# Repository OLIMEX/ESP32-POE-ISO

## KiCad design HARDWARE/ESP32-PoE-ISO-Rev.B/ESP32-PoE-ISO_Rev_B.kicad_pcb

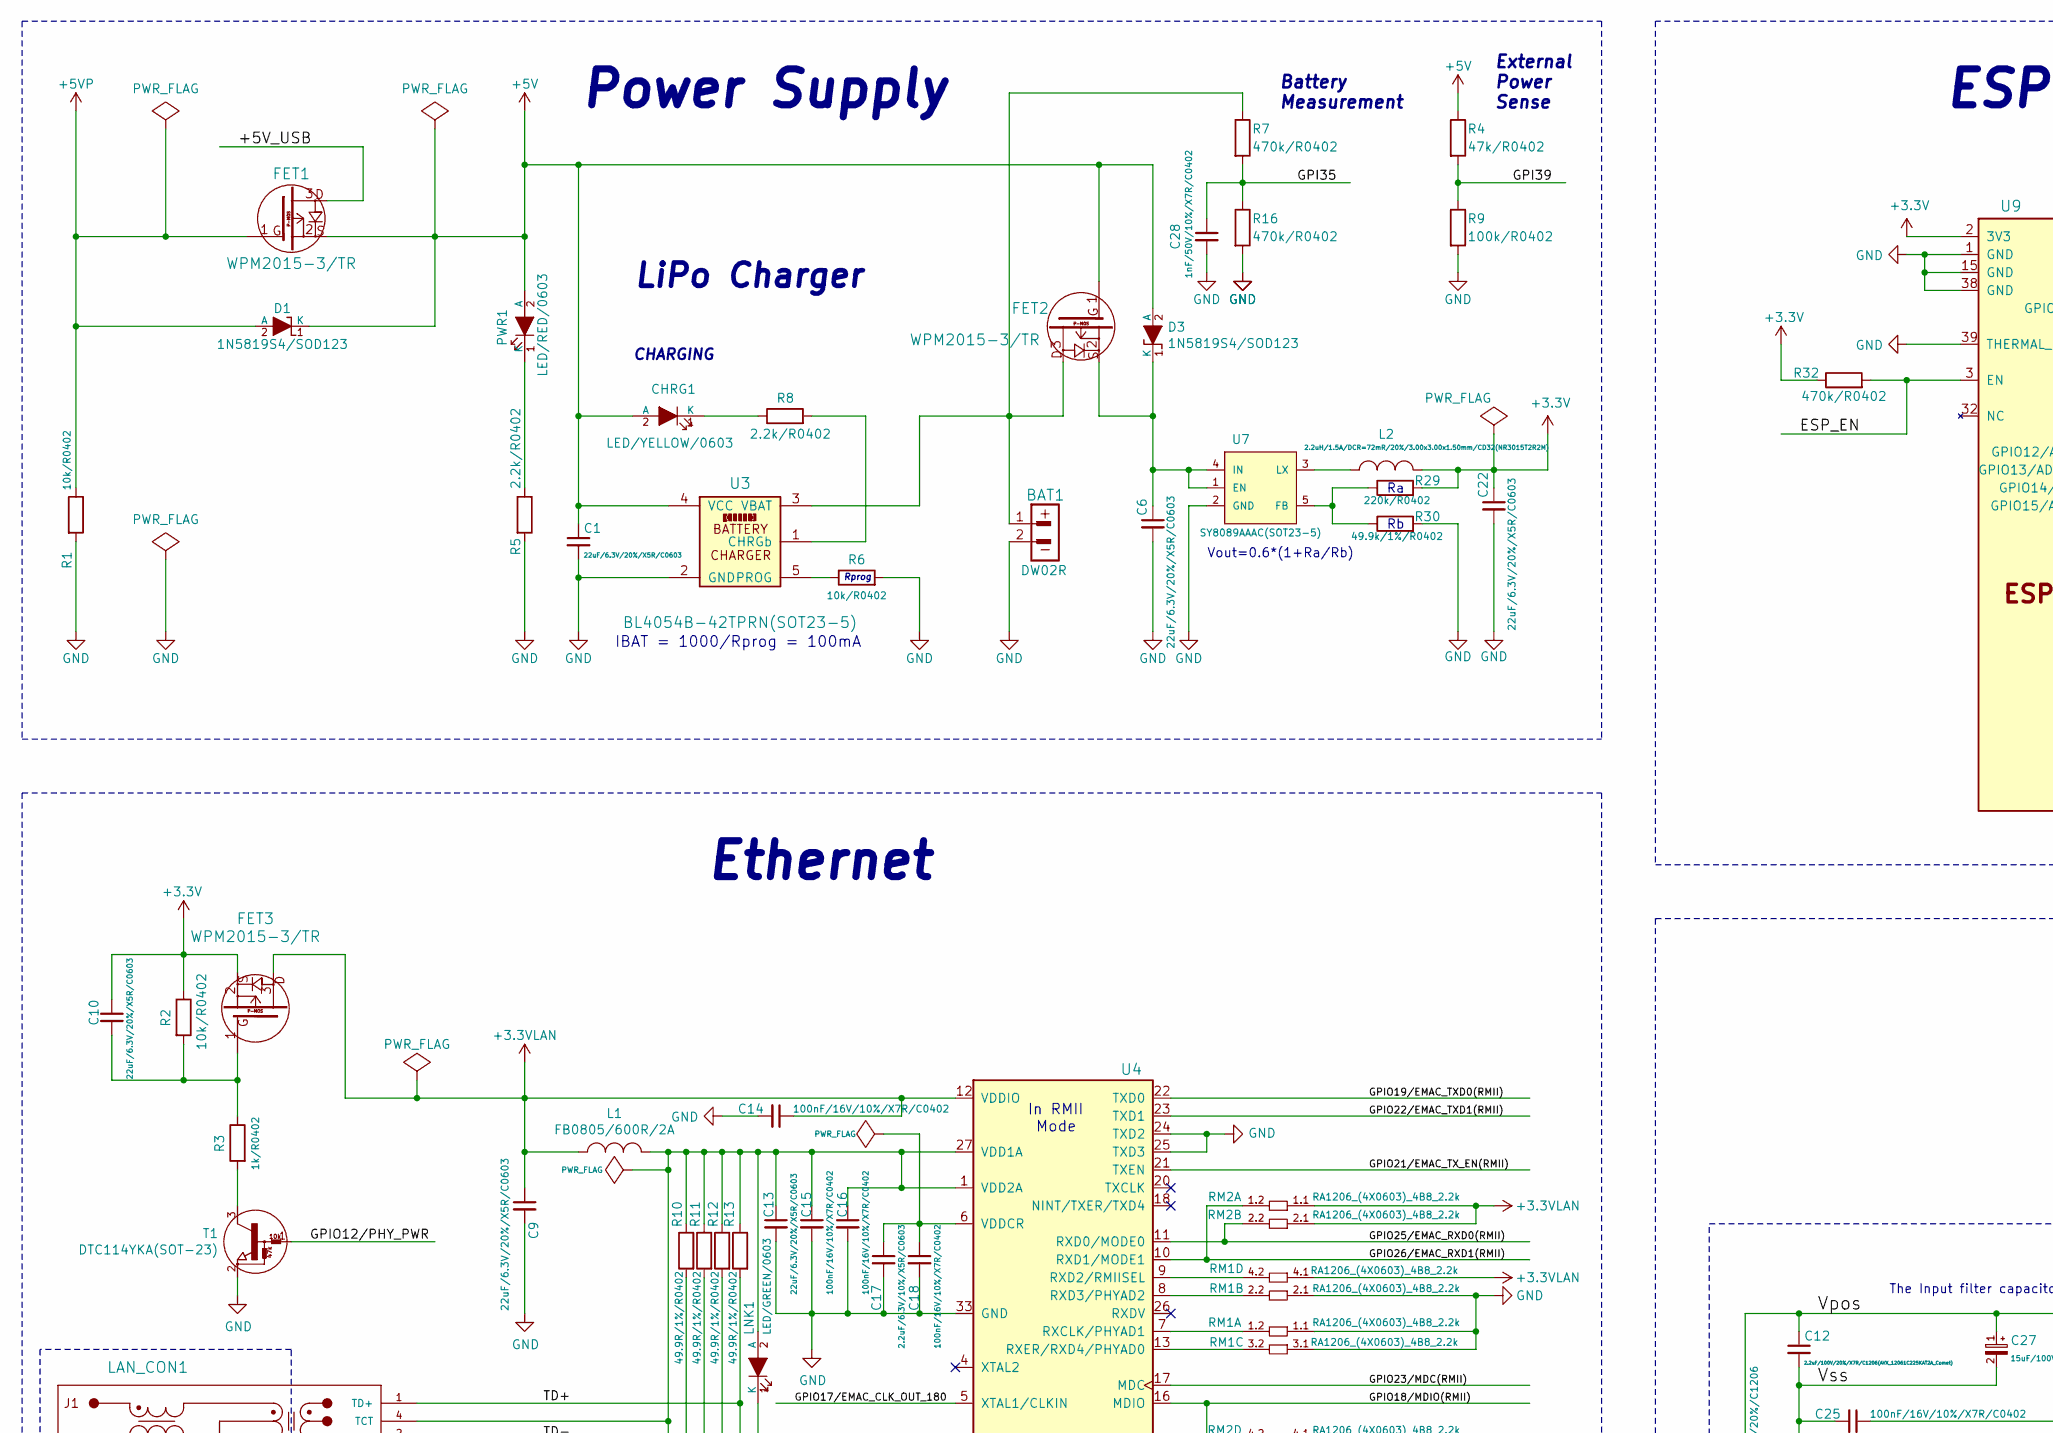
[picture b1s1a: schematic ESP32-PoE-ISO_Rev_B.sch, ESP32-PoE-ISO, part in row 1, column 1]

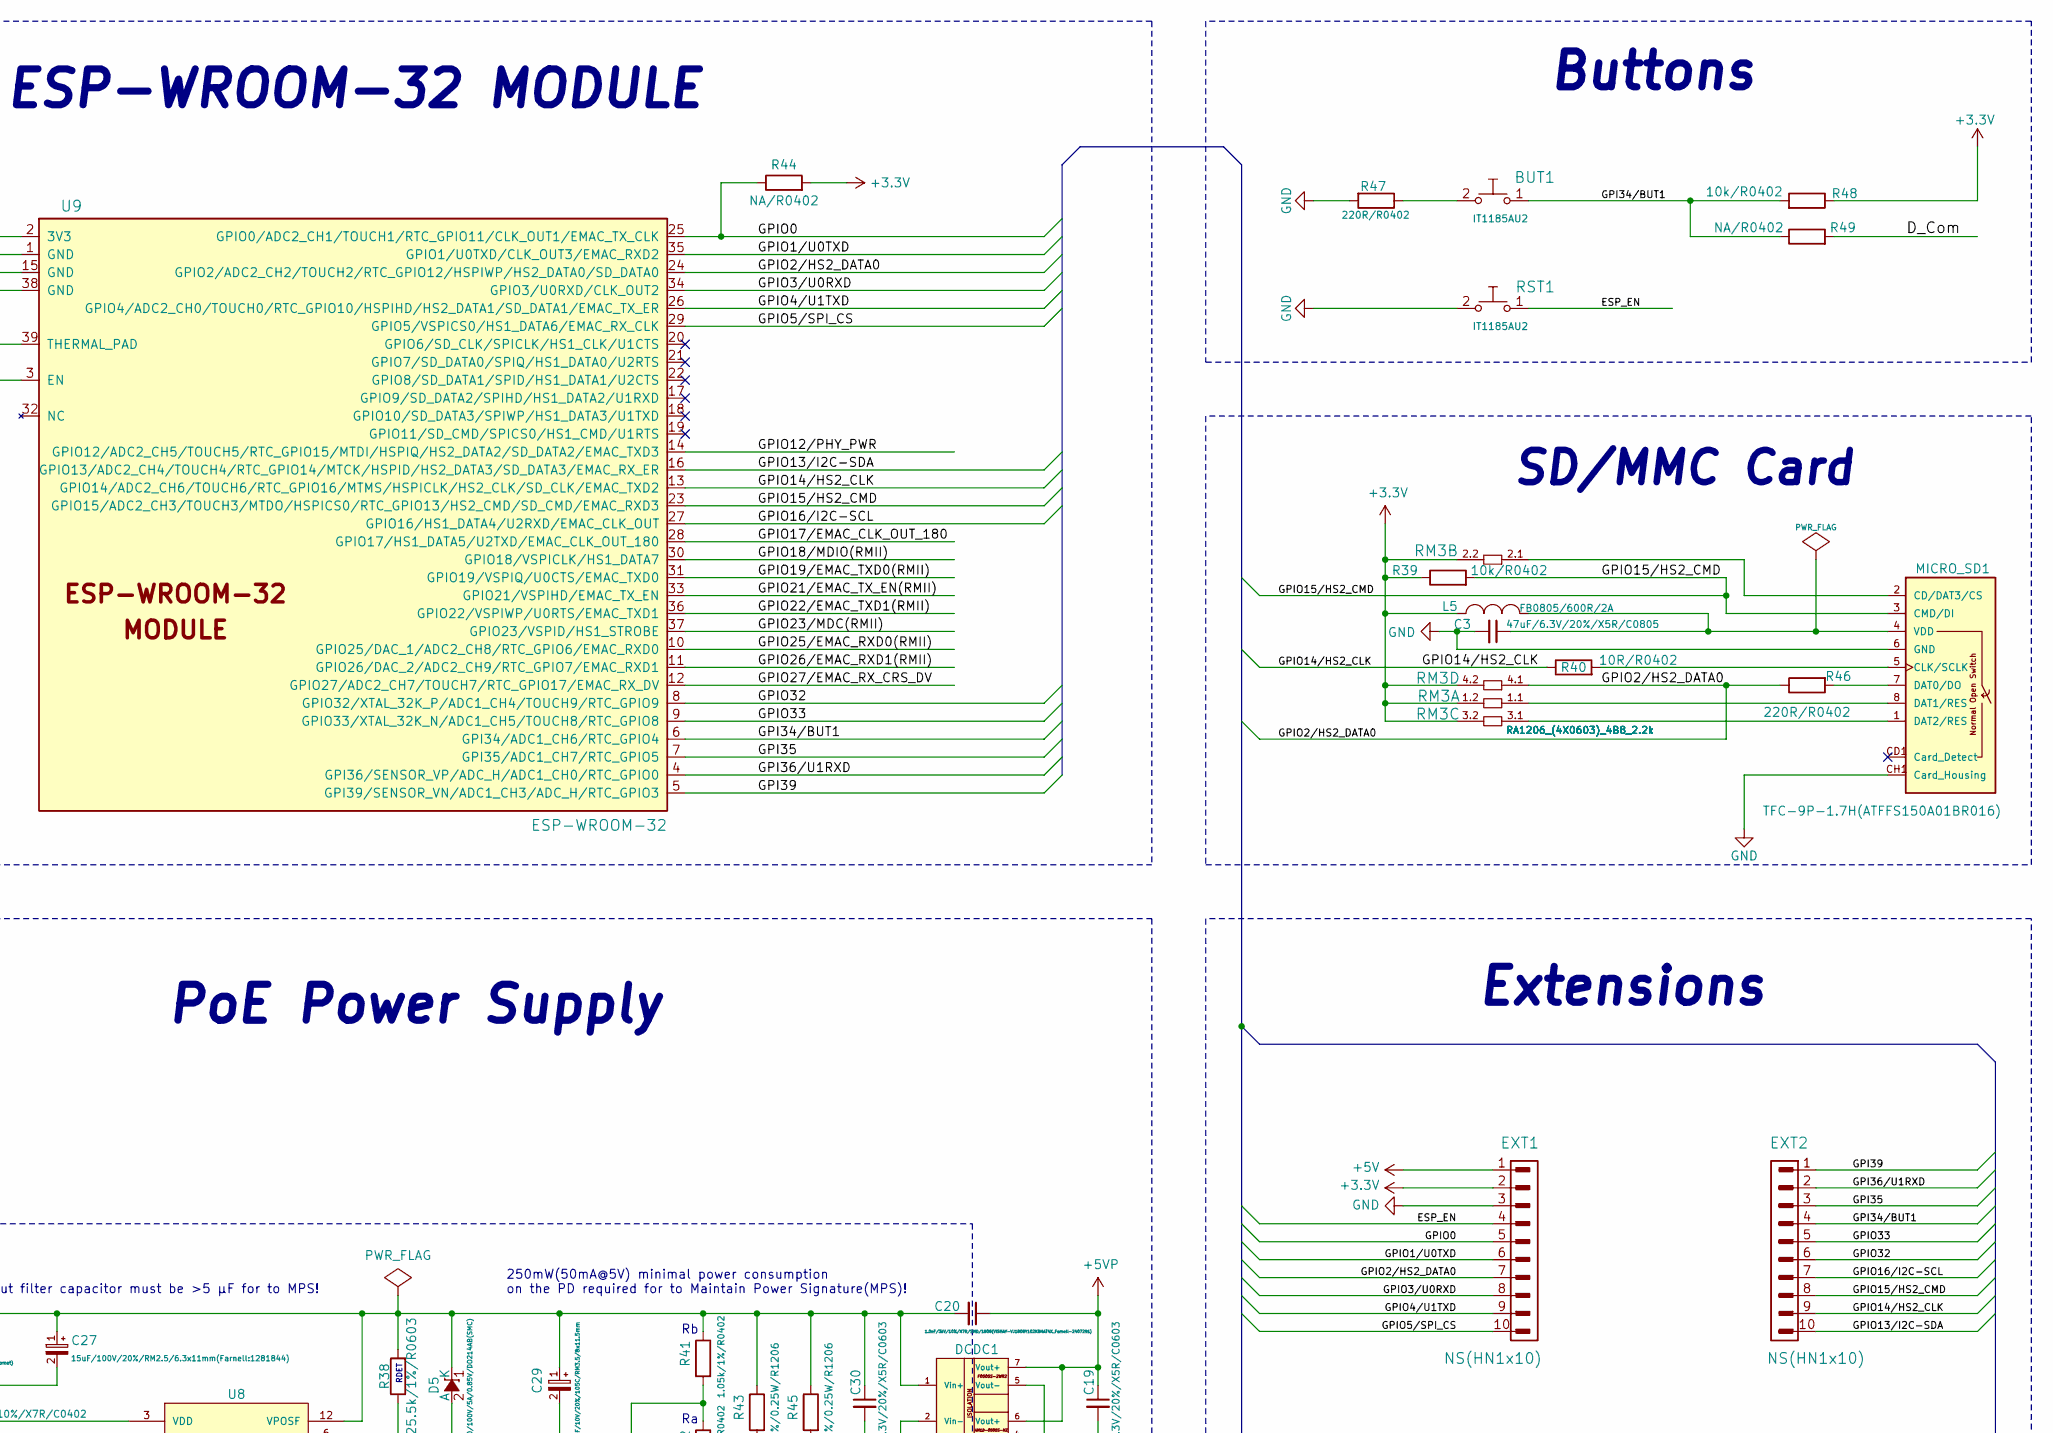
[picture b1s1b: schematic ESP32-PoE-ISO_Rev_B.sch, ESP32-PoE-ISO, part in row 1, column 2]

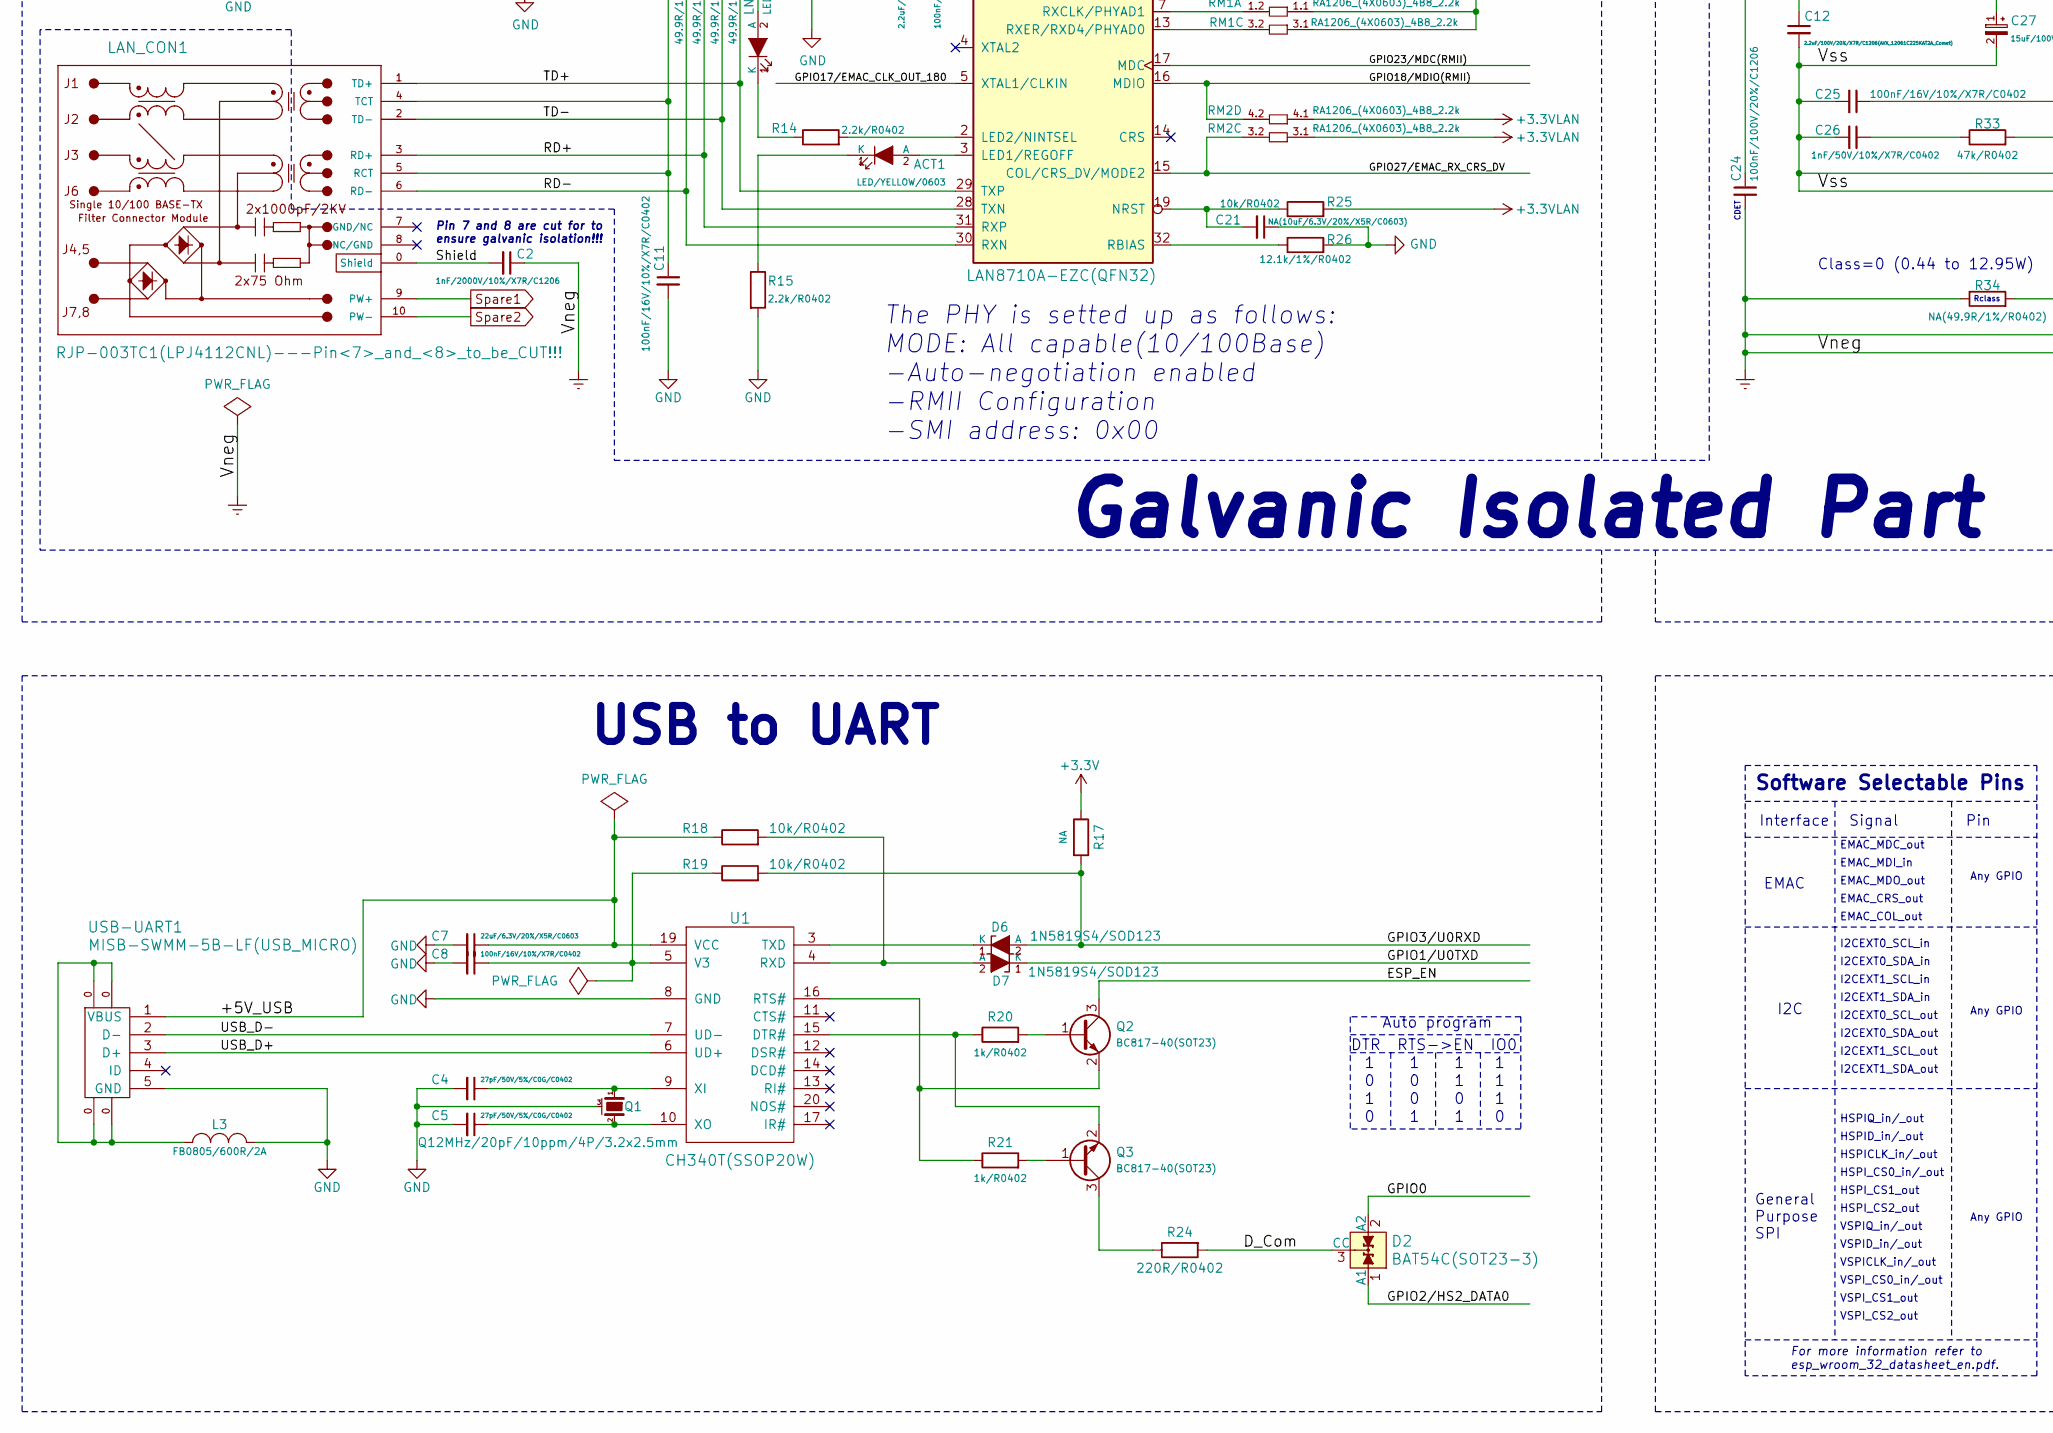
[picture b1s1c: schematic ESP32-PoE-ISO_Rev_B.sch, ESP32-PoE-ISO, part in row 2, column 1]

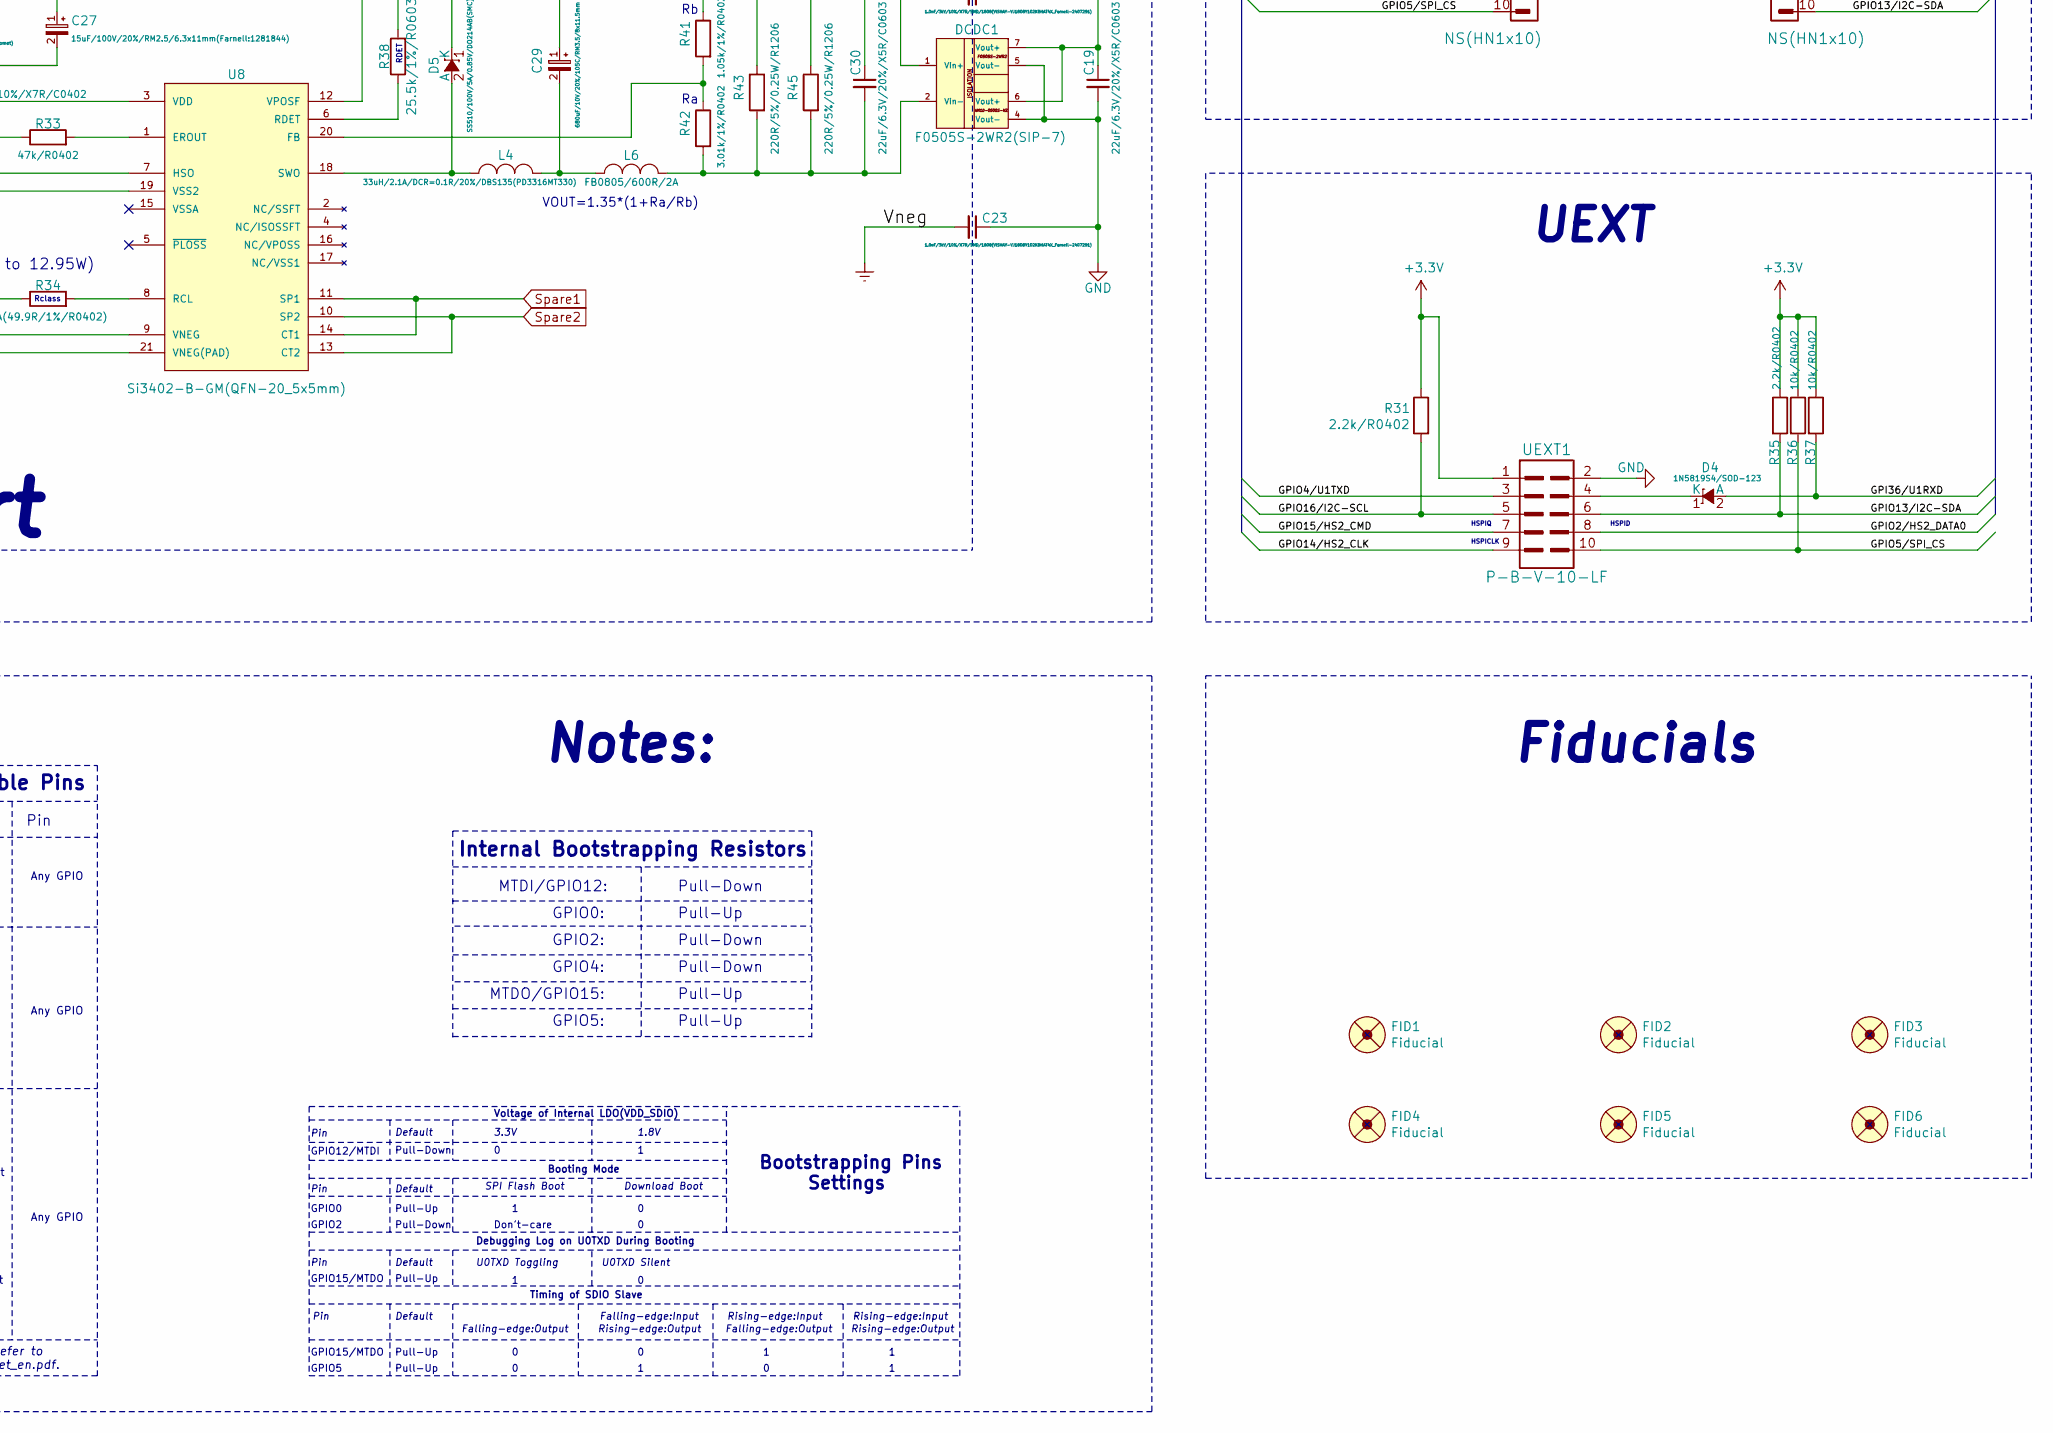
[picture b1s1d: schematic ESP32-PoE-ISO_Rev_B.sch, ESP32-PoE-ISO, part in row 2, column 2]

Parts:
ACT1: LED/YELLOW/0603; LED_0603_KA
BAT1: DW02R; LIPO_BAT-CON2DW02R
BUT1: IT1185AU2; IT1185AU2_V2
C1, C6, C7, C9, C10, C13, C19, C22, C30: 22uF/6.3V/20%/X5R/C0603; C_0603_5MIL_DWS
C2: 1nF/2000V/10%/X7R/C1206; C_1206_5MIL_DWS_ISO
C3: 47uF/6.3V/20%/X5R/C0805; C_0805_5MIL_DWS
C4, C5: 27pF/50V/5%/C0G/C0402; C_0402_5MIL_DWS
C8, C11, C14, C15, C16, C18, C25: 100nF/16V/10%/X7R/C0402; C_0402_5MIL_DWS
C12: 2.2uF/100V/20%/X7R/C1206(AVX_12061C225KAT2A_Comet); C_1206_5MIL_DWS_ISO
C17: 2.2uF/6.3V/10%/X5R/C0603; C_0603_5MIL_DWS
C20, C23: 1.0nF/3kV/10%/X7R/SMD/1808(VISHAY-VJ1808Y102KBHAT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; C_1808(4520)_5MIL_DWS_ISO
C21: NA(10uF/6.3V/20%/X5R/C0603); C_0603_5MIL_DWS
C24: 100nF/100V/20%/C1206; C_1206_5MIL_DWS
C26, C28: 1nF/50V/10%/X7R/C0402; C_0402_5MIL_DWS
C27: 15uF/100V/20%/RM2.5/6.3x11mm(Farnell:1281844); CPOL-RM2.5mm_6.3x11mm_PTH
C29: 680uF/10V/20%/105C/RM3.5/8x11.5mm; CPOL-RM3.5mm_8.0x11.5mm_PTH
CHRG1: LED/YELLOW/0603; LED_0603_KA
D1, D3, D6, D7: 1N5819S4/SOD123; SOD-123_1C-2A_KA
D2: BAT54C(SOT23-3); SOT23-3
D4: 1N5819S4/SOD-123; SOD-123_1C-2A_KA
D5: SS510/100V/5A/0.85V/DO214AB(SMC); DO214AB(SMC)_1(K)-2(A)
DCDC1: F0505S-2WR2(SIP-7); SIP-7_Universal
EXT1, EXT2: NS(HN1x10); HN1x10
FET1, FET2, FET3: WPM2015-3/TR; SOT23
FID1, FID2, FID3, FID4, FID5, FID6: Fiducial; Fiducial1x3
L1, L3, L5, L6: FB0805/600R/2A; L_0805_5MIL_DWS
L2: 2.2uH/1.5A/DCR=72mR/20%/3.00x3.00x1.50mm/CD32(NR3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; CD32
L4: 33uH/2.1A/DCR=0.1R/20%/DBS135(PD3316MT330); DBS135
LAN_CON1: RJP-003TC1(LPJ4112CNL)---Pin<7>_and_<8>_to_be_CUT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; RJP-003TC1(LPJ4112CNL)-ISO(Pin(7)and(8)CUT)
LNK1: LED/GREEN/0603; LED_0603_KA
MICRO_SD1: TFC-9P-1.7H(ATFFS150A01BR016); uSD(TFC-9P-1.xH(ATFFS150A01BR016))
PWR1: LED/RED/0603; LED_0603_KA
Q1: Q12MHz/20pF/10ppm/4P/3.2x2.5mm; TSX-3.2x2.5mm_GND(3)
Q2, Q3: BC817-40(SOT23); SOT23
R1, R2, R6, R18, R19, R25, R36, R37, R39, R48: 10k/R0402; R_0402_5MIL_DWS
R3, R20, R21: 1k/R0402; R_0402_5MIL_DWS
R4, R33: 47k/R0402; R_0402_5MIL_DWS
R5, R8, R14, R15, R31, R35: 2.2k/R0402; R_0402_5MIL_DWS
R7, R16, R32: 470k/R0402; R_0402_5MIL_DWS
R9: 100k/R0402; R_0402_5MIL_DWS
R10, R11, R12, R13: 49.9R/1%/R0402; R_0402_5MIL_DWS
R17: NA; R_0402_5MIL_DWS
R24, R46, R47: 220R/R0402; R_0402_5MIL_DWS
R26: 12.1k/1%/R0402; R_0402_5MIL_DWS
R29: 220k/R0402; R_0402_5MIL_DWS
R30: 49.9k/1%/R0402; R_0402_5MIL_DWS
R34: NA(49.9R/1%/R0402); R_0402_5MIL_DWS
R38: 25.5k/1%/R0603; R_0603_5MIL_DWS
R40: 10R/R0402; R_0402_5MIL_DWS
R41: 1.05k/1%/R0402; R_0402_5MIL_DWS
R42: 3.01k/1%/R0402; R_0402_5MIL_DWS
R43, R45: 220R/5%/0.25W/R1206; R_1206_5MIL_DWS
R44, R49: NA/R0402; R_0402_5MIL_DWS
RM1, RM2, RM3: RA1206_(4X0603)_4B8_2.2k; R_MATRIX_4
RST1: IT1185AU2; IT1185AU2_V2
T1: DTC114YKA(SOT-23); SOT23
U1: CH340T(SSOP20W); SSOP-20W
U3: BL4054B-42TPRN(SOT23-5); SOT-23-5
U4: LAN8710A-EZC(QFN32); QFN32_EP(33)_5.00x5.00x0.90mm_Pitch_0.50mm
U7: SY8089AAAC(SOT23-5); SOT-23-5
U8: Si3402-B-GM(QFN-20_5x5mm); QFN-20_5x5mm(Si3402-B-GM)
U9: ESP-WROOM-32; ESP-WROOM-32_MODULE
UEXT1: P-B-V-10-LF; GBH-254-SMT-10
USB-UART1: MISB-SWMM-5B-LF(USB_MICRO); USB-MICRO_MISB-SWMM-5B_LF

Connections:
+3.3VLAN: C9.1, C14.1, FET3.3, L1.1, R25.2, RM1.4.1, RM2.1.1, RM2.2.1, RM2.3.1, RM2.4.1, U4.12 (VDDIO)
+3V3: C10.1, C22.1, EXT1.2, FET3.2, L2.2, L5.1, R2.1, R17.1, R29.2, R31.1, R32.1, R35.1, R36.1, R37.1, R39.1, R44.2, R48.1, RM3.1.2, RM3.2.2, RM3.3.2, RM3.4.2, U9.2 (3V3), UEXT1.1
+5V: C1.1, CHRG1.2 (A), D1.1 (K), D3.2 (A), EXT1.1, FET1.2, FET2.1, PWR1.2 (A), R4.1, U3.4 (VCC)
+5VP: C19.1, C20.1, D1.2 (A), DCDC1.6 (Vout+), DCDC1.7 (Vout+), FET1.1, R1.1
/+5V_USB: C7.1, FET1.3, R18.1, U1.19 (VCC), USB-UART1.1 (VBUS)
/D_Com: D2.3 (CC), R24.2, R49.2
/ESP_EN: EXT1.4, Q2.3 (C), R32.2, RST1.1, U9.3 (EN)
/GPI34/BUT1: BUT1.1, EXT2.4, R48.2, R49.1, U9.6 (GPI34/ADC1_CH6/RTC_GPIO4)
/GPI35: C28.1, EXT2.3, R7.2, R16.1, U9.7 (GPI35/ADC1_CH7/RTC_GPIO5)
/GPI36/U1RXD: D4.2 (A), EXT2.2, R37.2, U9.4 (GPI36/SENSOR_VP/ADC_H/ADC1_CH0/RTC_GPIO0)
/GPI39: EXT2.1, R4.2, R9.1, U9.5 (GPI39/SENSOR_VN/ADC1_CH3/ADC_H/RTC_GPIO3)
/GPIO0: D2.2 (A2), EXT1.5, R44.1, U9.25 (GPIO0/ADC2_CH1/TOUCH1/RTC_GPIO11/CLK_OU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)
/GPIO1/U0TXD: D7.1 (K), EXT1.6, U9.35 (GPIO1/U0TXD/CLK_OUT3/EMAC_RXD2)
/GPIO2/HS2_DATA0: D2.1 (A1), EXT1.7, R46.1, RM3.4.1, U9.24 (GPIO2/ADC2_CH2/TOUCH2/RTC_GPIO12/HSPIWP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), UEXT1.8
/GPIO3/U0RXD: D6.2 (A), EXT1.8, R17.2, R19.2, U9.34 (GPIO3/U0RXD/CLK_OUT2)
/GPIO4/U1TXD: EXT1.9, U9.26 (GPIO4/ADC2_CH0/TOUCH0/RTC_GPIO10/HSPIHD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), UEXT1.3
/GPIO5/SPI_CS: EXT1.10, R36.2, U9.29 (GPIO5/VSPICS0/HS1_DATA6/EMAC_RX_CLK), UEXT1.10
/GPIO12/PHY_PWR: T1.1 (B), U9.14 (GPIO12/ADC2_CH5/TOUCH5/RTC_GPIO15/MTDI/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)
/GPIO13/I2C-SDA: EXT2.10, R35.2, U9.16 (GPIO13/ADC2_CH4/TOUCH4/RTC_GPIO14/MTCK/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), UEXT1.6
/GPIO14/HS2_CLK: EXT2.9, R40.1, U9.13 (GPIO14/ADC2_CH6/TOUCH6/RTC_GPIO16/MTMS/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), UEXT1.9
/GPIO15/HS2_CMD: EXT2.8, MICRO_SD1.3 (CMD/DI), R39.2, U9.23 (GPIO15/ADC2_CH3/TOUCH3/MTDO/HSPICS0/RTC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), UEXT1.7
/GPIO16/I2C-SCL: EXT2.7, R31.2, U9.27 (GPIO16/HS1_DATA4/U2RXD/EMAC_CLK_OUT), UEXT1.5
/GPIO17/EMAC_CLK_OUT_180: U4.5 (XTAL1/CLKIN), U9.28 (GPIO17/HS1_DATA5/U2TXD/EMAC_CLK_OUT_180)
/GPIO18/MDIO(RMII): RM2.4.2, U4.16 (MDIO), U9.30 (GPIO18/VSPICLK/HS1_DATA7)
/GPIO19/EMAC_TXD0(RMII): U4.22 (TXD0), U9.31 (GPIO19/VSPIQ/U0CTS/EMAC_TXD0)
/GPIO21/EMAC_TX_EN(RMII): U4.21 (TXEN), U9.33 (GPIO21/VSPIHD/EMAC_TX_EN)
/GPIO22/EMAC_TXD1(RMII): U4.23 (TXD1), U9.36 (GPIO22/VSPIWP/U0RTS/EMAC_TXD1)
/GPIO23/MDC(RMII): U4.17 (MDC), U9.37 (GPIO23/VSPID/HS1_STROBE)
/GPIO25/EMAC_RXD0(RMII): RM2.2.2, U4.11 (RXD0/MODE0), U9.10 (GPIO25/DAC_1/ADC2_CH8/RTC_GPIO6/EMAC_RX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)
/GPIO26/EMAC_RXD1(RMII): RM2.1.2, U4.10 (RXD1/MODE1), U9.11 (GPIO26/DAC_2/ADC2_CH9/RTC_GPIO7/EMAC_RX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)
/GPIO27/EMAC_RX_CRS_DV: RM2.3.2, U4.15 (COL/CRS_DV/MODE2), U9.12 (GPIO27/ADC2_CH7/TOUCH7/RTC_GPIO17/EMAC_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)
/GPIO32: EXT2.6, U9.8 (GPIO32/XTAL_32K_P/ADC1_CH4/TOUCH9/RTC_G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)
/GPIO33: EXT2.5, U9.9 (GPIO33/XTAL_32K_N/ADC1_CH5/TOUCH8/RTC_G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)
/RD+: LAN_CON1.3 (RD+), R11.2, U4.31 (RXP)
/RD-: LAN_CON1.6 (RD-), R10.2, U4.30 (RXN)
/Shield: C2.2, LAN_CON1.0 (Shield)
/TD+: LAN_CON1.1 (TD+), R13.2, U4.29 (TXP)
/TD-: LAN_CON1.2 (TD-), R12.2, U4.28 (TXN)
/USB_D+: U1.6 (UD+), USB-UART1.3 (D+)
/USB_D-: U1.7 (UD-), USB-UART1.2 (D-)
/Vpos: C12.1, C20.2, C24.1, C27.1 (+), C29.1 (+), C30.1, D5.1 (K), DCDC1.1 (Vin+), R38.2, R41.1, R43.1, R45.1, U8.12 (VPOSF)
/Vss: C12.2, C25.2, C26.2, C27.2 (-), U8.7 (HSO), U8.19 (VSS2)
Earth: C2.1, C23.2, C24.2, R34.1, U8.9 (VNEG), U8.21 (VNEG(PAD))
GND: BAT1.2, C1.2, C3.2, C4.2, C5.2, C6.2, C7.2, C8.2, C9.2, C11.2, C13.2, C14.2, C15.2, C16.2, C17.2, C18.2, C19.2, C21.1, C22.2, C23.1, C28.2, DCDC1.4 (Vout-), DCDC1.5 (Vout-), EXT1.3, L3.2, MICRO_SD1.6 (GND), MICRO_SD1.CH1 (Card_Housing), Q1.3 (case), R1.2, R5.2, R6.2, R9.2, R15.2, R16.2, R26.2, R30.2, R47.2, RM1.1.1, RM1.2.1, RM1.3.1, RST1.2, T1.2 (E), U1.8 (GND), U3.2 (GND), U4.24 (TXD2), U4.25 (TXD3), U4.33 (GND), U7.2 (GND), U9.1 (GND), U9.15 (GND), U9.38 (GND), U9.39 (THERMAL_PAD), UEXT1.2, USB-UART1.5 (GND)
unnamed: ACT1.1 (K), R15.1
unnamed: ACT1.2 (A), U4.3 (LED1/REGOFF)
unnamed: BAT1.1, FET2.3, R7.1, U3.3 (VBAT)
unnamed: BUT1.2, R47.1
unnamed: C3.1, L5.2, MICRO_SD1.4 (VDD)
unnamed: C4.1, Q1.1, U1.9 (XI)
unnamed: C5.1, Q1.2, U1.10 (XO)
unnamed: C6.1, D3.1 (K), FET2.2, U7.1 (EN), U7.4 (IN)
unnamed: C8.1, R19.1, U1.5 (V3)
unnamed: C10.2, FET3.1, R2.2, R3.1
unnamed: C11.1, C13.1, C15.1, C16.1, L1.2, LAN_CON1.4 (TCT), LAN_CON1.5 (RCT), LNK1.2 (A), R10.1, R11.1, R12.1, R13.1, U4.1 (VDD2A), U4.27 (VDD1A)
unnamed: C17.1, C18.1, U4.6 (VDDCR)
unnamed: C21.2, R25.1, U4.19 (NRST)
unnamed: C25.1, U8.3 (VDD)
unnamed: C26.1, R33.1
unnamed: C29.2 (-), L4.2, L6.1
unnamed: C30.2, DCDC1.2 (Vin-), L6.2, R42.2, R43.2, R45.2
unnamed: CHRG1.1 (K), R8.1
unnamed: D4.1 (K), UEXT1.4
unnamed: D5.2 (A), L4.1, U8.18 (SWO)
unnamed: D6.1 (K), U1.3 (TXD)
unnamed: D7.2 (A), R18.2, U1.4 (RXD)
unnamed: L2.1, U7.3 (LX)
unnamed: L3.1, USB-UART1.0
unnamed: LNK1.1 (K), R14.1
unnamed: MICRO_SD1.1 (DAT2/RES), RM3.3.1
unnamed: MICRO_SD1.2 (CD/DAT3/CS), RM3.2.1
unnamed: MICRO_SD1.5 (CLK/SCLK), R40.2
unnamed: MICRO_SD1.7 (DAT0/DO), R46.2
unnamed: MICRO_SD1.8 (DAT1/RES), RM3.1.1
unnamed: PWR1.1 (K), R5.1
unnamed: Q2.1 (B), R20.2
unnamed: Q2.2 (E), R21.1, U1.16 (RTS#)
unnamed: Q3.1 (B), R21.2
unnamed: Q3.2 (E), R20.1, U1.15 (DTR#)
unnamed: Q3.3 (C), R24.1
unnamed: R3.2, T1.3 (C)
unnamed: R6.1, U3.5 (PROG)
unnamed: R8.2, U3.1 (CHRGb)
unnamed: R14.2, U4.2 (LED2/NINTSEL)
unnamed: R26.1, U4.32 (RBIAS)
unnamed: R29.1, R30.1, U7.5 (FB)
unnamed: R33.2, U8.1 (EROUT)
unnamed: R34.2, U8.8 (RCL)
unnamed: R38.1, U8.6 (RDET)
unnamed: R41.2, R42.1, U8.20 (FB)
unnamed: RM1.1.2, U4.7 (RXCLK/PHYAD1)
unnamed: RM1.2.2, U4.8 (RXD3/PHYAD2)
unnamed: RM1.3.2, U4.13 (RXER/RXD4/PHYAD0)
unnamed: RM1.4.2, U4.9 (RXD2/RMIISEL)
Spare1: LAN_CON1.9 (PW+), U8.11 (SP1), U8.14 (CT1)
Spare2: LAN_CON1.10 (PW-), U8.10 (SP2), U8.13 (CT2)

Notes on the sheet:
Vout=0.6*(1+Ra/Rb)
Power Supply
Buttons
UEXT
In RMII Mode
Ethernet
ESP-WROOM-32 MODULE
SD/MMC Card
Bootstrapping Pins Settings
Internal Bootstrapping Resistors
MTDI/GPIO12:
Pull-Down
GPIO0:
Pull-Up
GPIO2:
GPIO4:
MTDO/GPIO15:
GPIO5:
Voltage of Internal LDO(VDD_SDIO)
Pin
Default
3.3V
1.8V
Booting Mode
GPIO12/MTDI
GPIO0
GPIO2
SPI Flash Boot
Download Boot
Don't-care
Debugging Log on U0TXD During Booting
U0TXD Toggling
U0TXD Silent
GPIO15/MTDO
Timing of SDIO Slave
For more information refer to esp_wroom_32_datasheet_en.pdf.
Falling-edge:Output
Falling-edge:Input
Rising-edge:Output
Rising-edge:Input

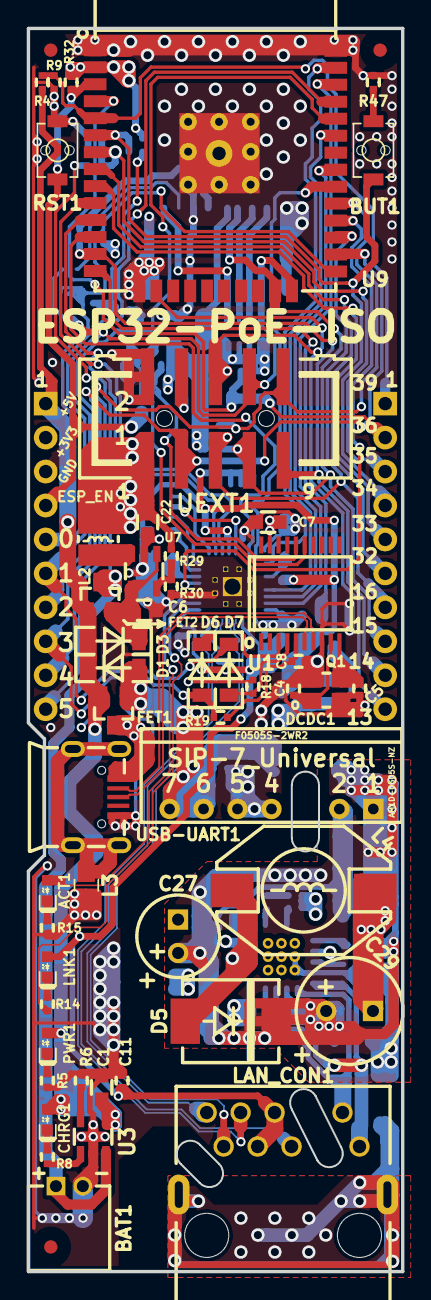
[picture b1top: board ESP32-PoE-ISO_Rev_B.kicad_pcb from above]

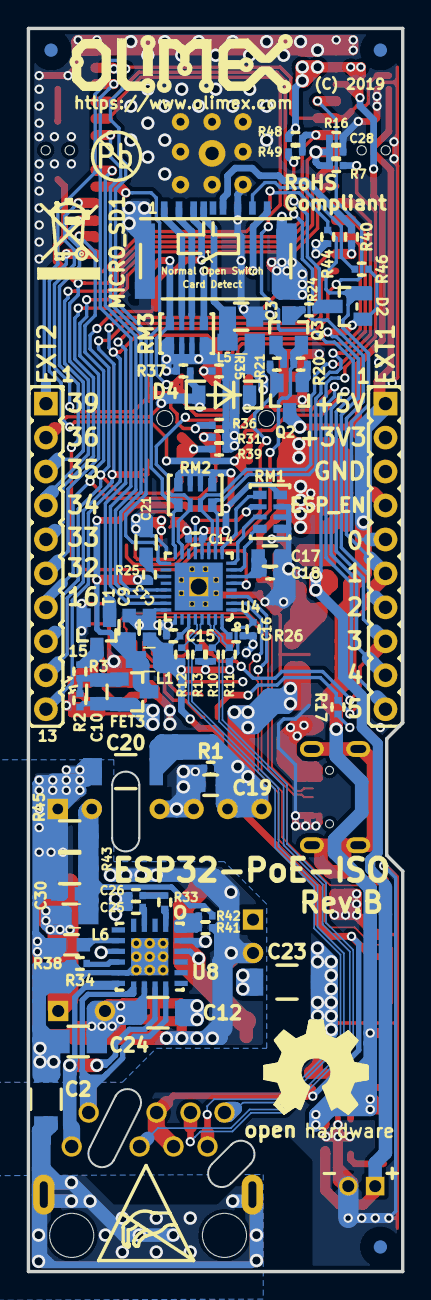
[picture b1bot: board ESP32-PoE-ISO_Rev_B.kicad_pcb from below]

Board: 4 copper layers, 28.0 x 93.0 mm, 132 parts (77 on the bottom side), 96 nets.

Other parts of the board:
Drill_Slot1, Drill_Slot2, Drill_Slot3: 2 mm; Mounting_hole_2_mm
Logo_OSHW: LOGO_OPENHARDWARE_8x8
Logo_Olimex: OLIMEX_LOGO_TB
Sign_Antistatic: Val**; LOGO_ANTISTATIC_1
Sign_PB-Free: LOGO_PBFREE
Sign_RecycleBin: LOGO_RECYCLEBIN_1

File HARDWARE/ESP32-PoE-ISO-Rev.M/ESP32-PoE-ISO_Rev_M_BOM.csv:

Quantity,Value,Footprint,Reference
2,LED/YELLOW/0603,LED_0603_KA,"ACT1, CHRG1"
1,DW02S,LIPO_BAT_VERTICAL_DW02S,BAT1
2,IT1185AU2,IT1185AU2_V2,"BUT1, RST1"
8,22uF/6.3V/20%/X5R/C0603,C_0603_5MIL_DWS,"C1, C6, C7, C9, C10, C13, C19, C22"
1,1nF/2000V/10%/X7R/C1206,C_1206_5MIL_DWS_ISO,C2
1,47uF/6.3V/20%/X5R/C0805,C_0805_5MIL_DWS,C3
6,100nF/10V/20%/X5R/C0402,C_0402_5MIL_DWS,"C8, C11, C14, C15, C16, C18"
2,100nF/100V/10%/X7R/C0603,C_0603_5MIL_DWS,"C12, C24"
1,2.2uF/6.3V/10%/X5R/C0603,C_0603_5MIL_DWS,C17
1,1.0nF/3kV/10%/X7R/SMD/1808(VISHAY-VJ1808Y102KBHAT4X_Farnell-2407291),C_1808(4520)_5MIL_DWS_ISO,C23
1,12pF/50V/5%/COG/C0402,C_0402_5MIL_DWS,C25
1,470uF/10V/20%/Low_ESR/RM2.5/6.0x11mm,CPOL-RM2.5mm_6.3x11mm_PTH,C26
1,15uF/100V/20%/RM2.5/6.3x11mm(Farnell:1281844),CPOL-RM2.5mm_6.3x11mm_PTH,C27
1,1nF/50V/10%/X7R/C0402,C_0402_5MIL_DWS,C28
1,1uF/10V/10%/X5R/C0603,C_0603_5MIL_DWS,C31
6,1N5819S4/SOD123,SOD-123_1C-2A_KA,"D1, D3, D4, D6, D7, D9"
1,BAT54C(SOT23-3),SOT23-3,D2
1,SS510/100V/5A/0.85V/DO214AB(SMC),DO214AB(SMC)_1(K)-2(A),D5
1,SMAJ58A/SMA,SMA-KA,D10
1,F0505S-2WR2(SIP-7),SIP-7_Universal,DCDC1
2,HN1x10,HN1x10,"EXT1, EXT2"
3,WPM2015-3/TR,SOT23,"FET1, FET2, FET3"
3,FB0805/600R/2A,L_0805_5MIL_DWS,"L1, L3, L5"
1,1.0uH/4.2A/DCR=35mR/20%/2.00x1.60x1.00mm/L2016(PIM201610-1R0MTS00),L_2016_MM,L2
1,33uH/2.1A/DCR=0.1R/20%/DBS135(PD3316MT330),DBS135,L4
1,RJP-003TC1(LPJ4112CNL),RJP-003TC1(LPJ4112CNL),LAN_CON1
1,LED/GREEN/0603,LED_0603_KA,LNK1
1,TFC-9P-1.7H(ATFFS150A01BR016),uSD(TFC-9P-1.xH(ATFFS150A01BR016)),MICRO_SD1
1,LED/RED/0603,LED_0603_KA,PWR1
2,BC817-40(SOT23),SOT23,"Q2, Q3"
11,10k/R0402,R_0402_5MIL_DWS,"R1, R2, R6, R18, R19, R25, R32, R36, R37, R39, R48"
3,1k/R0402,R_0402_5MIL_DWS,"R3, R20, R21"
1,47k/R0402,R_0402_5MIL_DWS,R4
6,2.2k/R0402,R_0402_5MIL_DWS,"R5, R8, R14, R15, R31, R35"
2,470k/R0402,R_0402_5MIL_DWS,"R7, R16"
1,100k/R0402,R_0402_5MIL_DWS,R9
4,49.9R/1%/R0402,R_0402_5MIL_DWS,"R10, R11, R12, R13"
1,24.9k/1%/R0402,R_0402_5MIL_DWS,R22
1,1.27k/1%/62.5mW/R0402,R_0402_5MIL_DWS,R23
3,220R/R0402,R_0402_5MIL_DWS,"R24, R46, R47"
1,12.1k/1%/R0402,R_0402_5MIL_DWS,R26
2,9.1k/1W/R2512,R_2512_MM_DWS,"R27, R41"
1,0.03R/1%/R1206,R_1206_5MIL_DWS,R28
1,220k/R0402,R_0402_5MIL_DWS,R29
1,49.9k/1%/R0402,R_0402_5MIL_DWS,R30
1,4.7R/R0402,R_0402_5MIL_DWS,R33
1,10.5k/1%/R0402,R_0402_5MIL_DWS,R34
1,56.2k/1%/R0402,R_0402_5MIL_DWS,R38
1,10R/R0402,R_0402_5MIL_DWS,R40
1,4.7k/R0402,R_0402_5MIL_DWS,R43
3,RA1206_(4X0603)_4B8_2.2k,R_MATRIX_4,"RM1, RM2, RM3"
1,LMUN2211LT1G(SOT-23),SOT23,T1
1,ESDS314DBVR(SOT-23-5),SOT-23-5,TVS1
1,CH340X(MSOP-10),MSOP-10_Pitch-0.5mm_3.00x3.00x1.00mm,U1
1,TPS2378DDAR(HSOIC-8),ESOIC-8,U2
1,TP4054-42-SOT25-R(SOT23-5),SOT-23-5,U3
1,LAN8710A-EZC(QFN32),QFN32_EP(33)_5.00x5.00x0.90mm_Pitch_0.50mm,U4
1,TX4138(ESOIC-8),ESOIC-8,U5
1," 	
ESP32-WROOM-32E-N4",ESP32-WROVER_MODULE,U6
1,TPS62A02ADRLR(SOT-563-6),SOT-563-6,U7
1,P-B-V-10-LF,GBH-254-SMT-10,UEXT1
1,MISB-SWMM-5B-LF(USB_MICRO),USB-MICRO_MISB-SWMM-5B_LF,USB-UART1

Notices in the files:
HARDWARE/ESP32-PoE-ISO-Rev.B/ESP32-PoE-ISO_Rev_B.kicad_pcb:
(C) 2019
